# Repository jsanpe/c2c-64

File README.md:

# C2C-64
A Composite & S-Video to Component Video transcoder to feed older analog signals into your OSSC.

Designed with the C-64 in mind, it also supports composite and s-video signals from other systems, including the N64. A compatibility chart will soon be available in the wiki section of this project.

## Description

This is an open hardware implementation of a board to convert Composite and S-Video signals into Component video. The component output from C2C-64 can be directly connected to an OSSC, effectively adding compatibility with Composite and S-Video input to this great scaler.

C2C-64 was primarily design as a simple way to connect a C64 to and OSSC. Most of the testing has been done in this platform, and presets have been chosen with it in mind. I have conducted some tests with other machines (N64, SNES, Dreamcast), although not as extensive.

C2C-64 uses a simple pipeline of video decoder and encoder to transform the input composite or S-video signals into component video. What this means in practice is that the analog input is converted to digital format and fed to the encoder to transform it into a different analog signal. This conversion is NOT lossless. However, it enables anyone to conveniently hook such signals directly into the OSSC without tinkering with the internals of their devices. 

## Getting your C2C-64

This is an open project, in this repository you will find everything you need in order to build your own C2C-64.

It is important to note that building this requires ninja-grade soldering skills, especially to get those QFN ICs properly connected to the board. Also, sourcing some of the components may be a bit trickier than usual. In particular, the ADV7180 IC is unsupported by Analog anymore and probably AliExpress is the only place where it can be found at this point. There is an ADV7280(A) based version of the C2C (2R) that will be soon released, but the price of this IC is way more expensive.

I am in the process of building a first batch of 35 boards (version 1R3) that I will be selling to anyone interested in supporting the project. Reach me directly if you are interested (DM me directly through [twitter](https://twitter.com/jsanpe))

You can also support the project by donating through my KoFi page 

## Comparison to Koryuu

In terms of functionality, C2C-64 provides a similar experience to the commercial product [Koryuu](https://videogameperfection.com/products/koryuu-transcoder/). However, there are notable differences between C2C-64 and Koryuu:
- C2C-64 is fully Open and Free, both Software and Hardware. Note, C2C-64 is still WiP so some parts are either missing or still in beta.
- C2C-64 has been designed to be as affordable as possible. The PCB is a 50x50mm 4 layer design, for which you can normally get special deals on PCB manufacturers. With the current shortage of electronic parts, it is difficult to estimate the total BOM cost given the huge price fluctuations. It should be possible to get the board built for well under $50 in small amounts even in these adverse conditions (half the price of Koryuu).
- The video decoding IC in the C2C-64 is the older Adv7180, compared to the more modern Adv7280 of the Koryuu. I made extensive tests, and for the intent and purposes of this board I don't think the extra cost of Adv7280 (5x the price of Adv7180) is justified. This assumption holds as long as you connect the output to an OSSC, which has de-interlacing and scaling options way beyond the possibilities of the Adv7280. An Adv7280-based version of C2C-64  already exists and will be released at some point in the future (it needs more testing and firmware changes)
- C2C-64 adds a big number of usability features to the mix (described below) making it way more flexible in terms of configuration options

## User interface

One important improvement of C2C-64 over Koryuu is the inclusion of powerful interfacing options. The board provides three main ways of allowing user interaction:
- Side switches: There are 3 switches that allow the user to perform the two most common actions: alternating the source video signal between composite and S-video; and selecting configuration profiles stored in the board EEPROM.
- UART connection: A computer can be hooked up to the board using the uart pin headers available for this purpose. Using a VT100 compatible terminal, users can configure tenths of parameters about how the video decoding/encoding is performed using menus. Such settings can then be stored as profiles in the EEPROM to be easily accessed using the side switches.
- OLED Screen: The board supports the connection of an OPTIONAL 0.96'' oled display. When the board detected that an OLED display has been connected, it will show a reduced version of the menu system offered through the UART connection, making the use of a computer to configure settings completely unnecessary.

There are also 4 leds that are used to show important signals about the operation of the board

## Important notice

This project is still WiP. The repository contains only a beta version of the firmware required to run the board. Keep checking this page for updates.

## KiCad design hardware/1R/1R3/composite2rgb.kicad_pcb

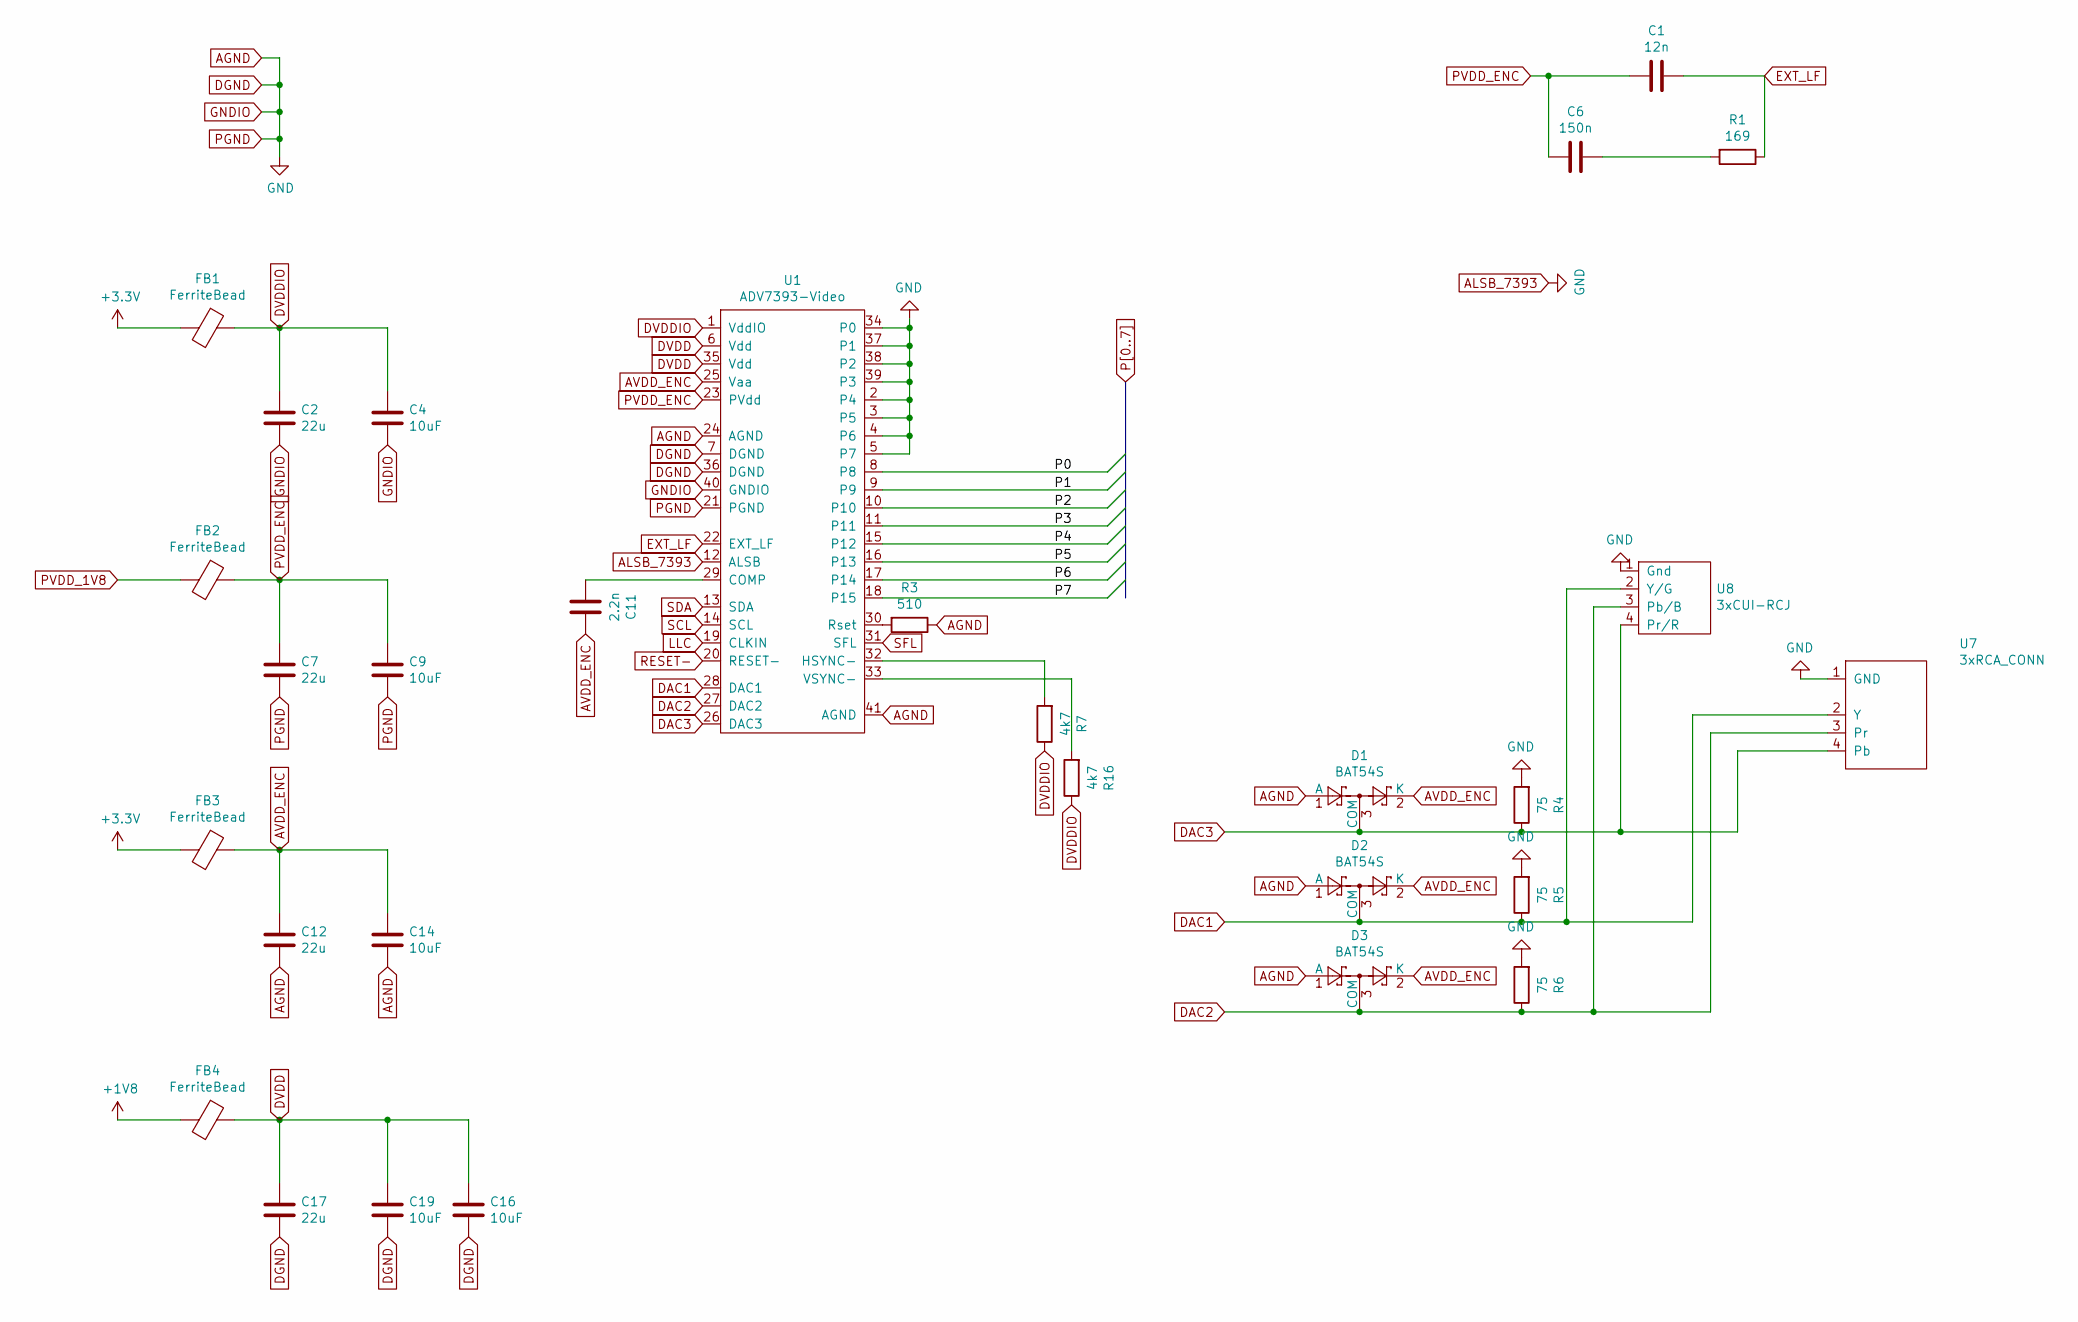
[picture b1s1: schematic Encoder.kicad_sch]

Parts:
C1: 12n; C_0603_1608Metric; LCSC_Part C1593
C2, C7, C12, C17: 22u; C_0805_2012Metric_Pad1.18x1.45mm_HandSolder; LCSC_Part C45783
C4, C9, C14, C16, C19: 10uF; C_0603_1608Metric; LCSC_Part C14663
C6: 150n; C_0603_1608Metric; LCSC_Part C21118
C11: 2.2n; C_0603_1608Metric; LCSC_Part C1604
D1, D2, D3: BAT54S; SOT-23
FB1, FB2, FB3, FB4: FerriteBead; L_0805_2012Metric; LCSC_Part C1015
R1: 169; R_0805_2012Metric; LCSC C22889
R3: 510; R_0805_2012Metric; LCSC C17734
R4, R5, R6: 75; R_0805_2012Metric; LCSC_Part C20638
R7, R16: 4k7; R_0603_1608Metric; LCSC_Part C23162
U1: ADV7393-Video; QFN-40-1EP_6x6mm_P0.5mm_EP4.6x4.6mm_ThermalVias; LCSC C662241
U7: 3xRCA_CONN; TRRS-PJ-320A
U8: 3xCUI-RCJ; 3xCUI_RCJ-041

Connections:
+1V8: FB4.2; also elsewhere on the board
+3.3V: FB1.2, FB3.2; also elsewhere on the board
AGND: C2.1, C4.1, C7.1, C9.1, C12.1, C14.1, C16.1, C17.1, C19.1, D1.1 (A), D2.1 (A), D3.1 (A), R3.1, R4.2, R5.2, R6.2, U1.2 (P4), U1.3 (P5), U1.4 (P6), U1.5 (P7), U1.7 (DGND), U1.12 (ALSB), U1.21 (PGND), U1.24 (AGND), U1.34 (P0), U1.36 (DGND), U1.37 (P1), U1.38 (P2), U1.39 (P3), U1.40 (GNDIO), U1.41 (AGND), U7.1 (GND), U8.1 (Gnd); also elsewhere on the board
AVDD_ENC: C11.2, C12.2, C14.2, D1.2 (K), D2.2 (K), D3.2 (K), FB3.1, U1.25 (Vaa)
DAC1: D2.3 (COM), R5.1, U1.28 (DAC1), U7.2 (Y), U8.2 (Y/G)
DAC2: D3.3 (COM), R6.1, U1.27 (DAC2), U7.3 (Pr), U8.3 (Pb/B)
DAC3: D1.3 (COM), R4.1, U1.26 (DAC3), U7.4 (Pb), U8.4 (Pr/R)
DVDD: C16.2, C17.2, C19.2, FB4.1, U1.6 (Vdd), U1.35 (Vdd); also elsewhere on the board
DVDDIO: C2.2, C4.2, FB1.1, R7.1, R16.1, U1.1 (VddIO); also elsewhere on the board
EXT_LF: C1.1, R1.1, U1.22 (EXT_LF)
LLC: U1.19 (CLKIN); also elsewhere on the board
unnamed: C6.1, R1.2
unnamed: C11.1, U1.29 (COMP)
unnamed: R7.2, U1.32 (HSYNC-)
unnamed: R3.2, U1.30 (Rset)
unnamed: R16.2, U1.33 (VSYNC-)
P0: U1.8; also elsewhere on the board
P1: U1.9; also elsewhere on the board
P2: U1.10; also elsewhere on the board
P3: U1.11; also elsewhere on the board
P4: U1.15 (P12); also elsewhere on the board
P5: U1.16 (P13); also elsewhere on the board
P6: U1.17 (P14); also elsewhere on the board
P7: U1.18 (P15); also elsewhere on the board
PVDD_1V8: FB2.2; also elsewhere on the board
PVDD_ENC: C1.2, C6.2, C7.2, C9.2, FB2.1, U1.23 (PVdd)
RESET-: U1.20 (RESET-); also elsewhere on the board
SCL: U1.14 (SCL); also elsewhere on the board
SDA: U1.13 (SDA); also elsewhere on the board
SFL: U1.31 (SFL); also elsewhere on the board

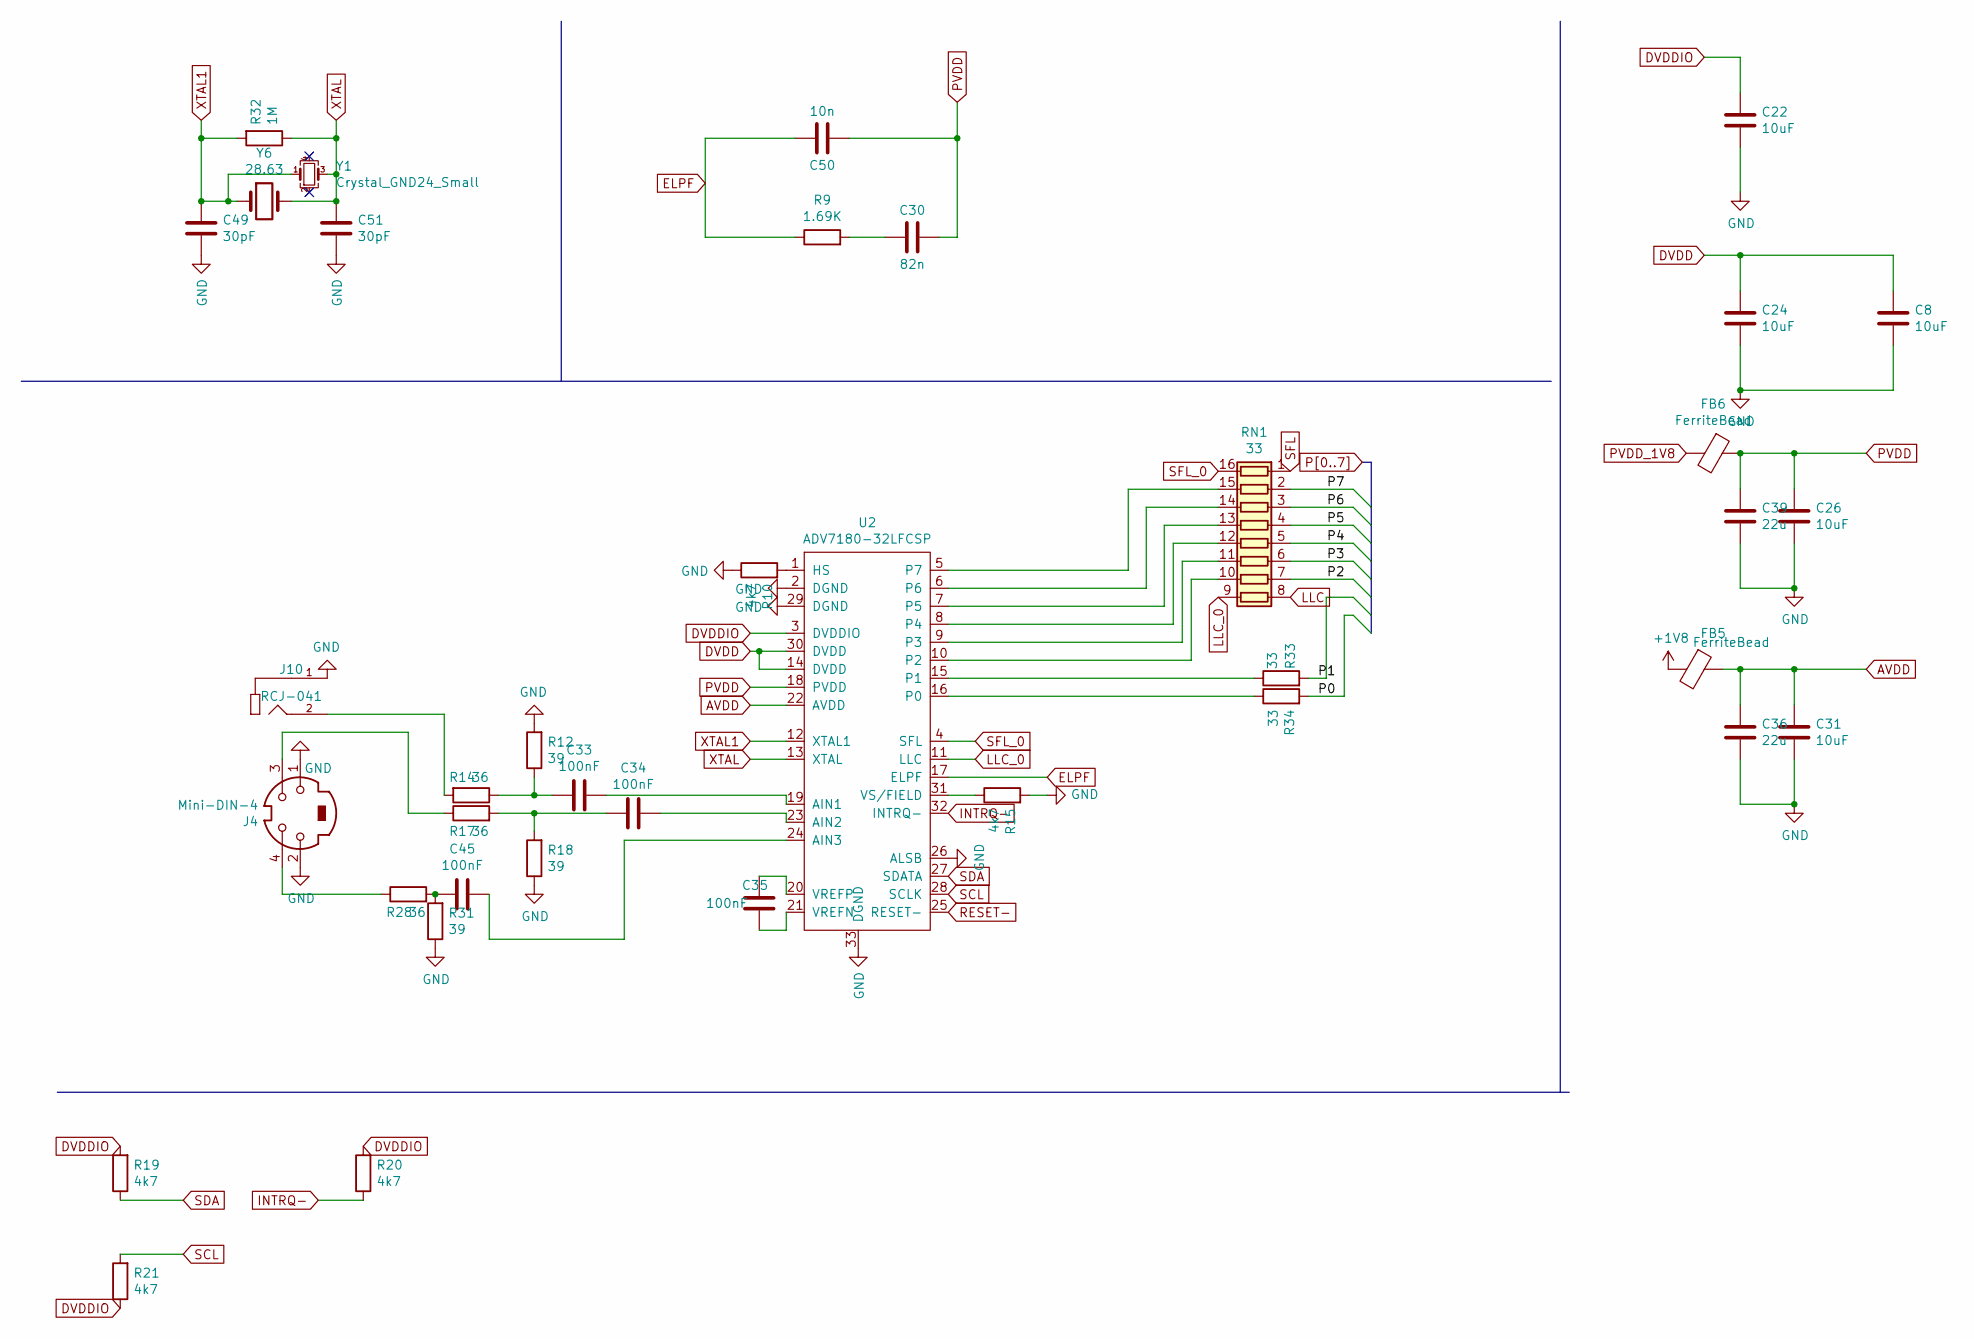
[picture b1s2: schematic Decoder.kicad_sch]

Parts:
C8, C22, C24, C26, C31: 10uF; C_0603_1608Metric; LCSC C19702
C30: 82n; C_0603_1608Metric; LCSC C107100
C33, C34, C35, C45: 100nF; C_0603_1608Metric; LCSC C14663
C36, C39: 22u; C_0805_2012Metric; LCSC C45783
C49, C51: 30pF; C_0603_1608Metric; LCSC_Part C57112
C50: 10n; C_0603_1608Metric; LCSC C57112
FB5, FB6: FerriteBead; L_0805_2012Metric; LCSC C1017
J4: Mini-DIN-4; CUI_MD-50S
J10: RCJ-041; CUI_RCJ-041
R9: 1.69K; R_0603_1608Metric; LCSC C22846
R10, R15, R19, R20, R21: 4k7; R_0603_1608Metric; LCSC C23162
R12, R18, R31: 39; R_0805_2012Metric; LCSC C186443
R14, R17, R28: 36; R_0805_2012Metric; LCSC C186442
R32: 1M; R_0603_1608Metric; LCSC C22935
R33, R34: 33; R_0805_2012Metric; LCSC C17634
RN1: 33; RESCAXE50P380X160X55-16N; LCSC C78520
U2: ADV7180-32LFCSP; LFCSP-32-1EP_5x5mm_P0.5mm_EP3.1x3.1mm_ThermalVias; LCSC C459884
Y1: Crystal_GND24_Small; Crystal_SMD_3225-4Pin_3.2x2.5mm; LCSC C136080
Y6: 28.63; Crystal_C38-LF_D3.0mm_L8.0mm_Vertical

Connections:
+1V8: FB5.2; also elsewhere on the board
AGND: C8.1, C22.1, C24.1, C26.1, C31.1, C36.1, C39.1, C49.1, C51.1, J4.1, J4.2, J10.1, R10.1, R12.2, R15.2, R18.1, R31.1, U2.2 (DGND), U2.26 (ALSB), U2.29 (DGND), U2.33 (DGND); also elsewhere on the board
AVDD: C31.2, C36.2, FB5.1, U2.22 (AVDD)
DVDD: C8.2, C24.2, U2.14 (DVDD), U2.30 (DVDD); also elsewhere on the board
DVDDIO: C22.2, R19.2, R20.2, R21.1, U2.3 (DVDDIO); also elsewhere on the board
ELPF: C50.2, R9.1, U2.17 (ELPF)
INTRQ-: R20.1, U2.32 (INTRQ-)
LLC: RN1.8 (R8.1); also elsewhere on the board
LLC_0: RN1.9 (R8.2), U2.11 (LLC)
unnamed: C30.1, R9.2
unnamed: C33.2, R12.1, R14.1
unnamed: C34.2, R17.2, R18.2
unnamed: C45.2, R28.2, R31.2
unnamed: J4.3, R17.1
unnamed: J4.4, R28.1
unnamed: J10.2, R14.2
unnamed: RN1.15 (R2.2), U2.5 (P7)
unnamed: RN1.14 (R3.2), U2.6
unnamed: RN1.13 (R4.2), U2.7 (P5)
unnamed: RN1.12 (R5.2), U2.8 (P4)
unnamed: RN1.11 (R6.2), U2.9 (P3)
unnamed: RN1.10 (R7.2), U2.10 (P2)
unnamed: C33.1, U2.19 (AIN1)
unnamed: C34.1, U2.23 (AIN2)
unnamed: C45.1, U2.24 (AIN3)
unnamed: R10.2, U2.1 (HS)
unnamed: R34.1, U2.16 (P0)
unnamed: R33.1, U2.15 (P1)
unnamed: C35.2, U2.21 (VREFN)
unnamed: C35.1, U2.20 (VREFP)
unnamed: R15.1, U2.31 (VS/FIELD)
P0: R34.2; also elsewhere on the board
P1: R33.2; also elsewhere on the board
P2: RN1.7 (R7.1); also elsewhere on the board
P3: RN1.6 (R6.1); also elsewhere on the board
P4: RN1.5 (R5.1); also elsewhere on the board
P5: RN1.4 (R4.1); also elsewhere on the board
P6: RN1.3 (R3.1); also elsewhere on the board
P7: RN1.2 (R2.1); also elsewhere on the board
PVDD: C26.2, C30.2, C39.2, C50.1, FB6.1, U2.18 (PVDD)
PVDD_1V8: FB6.2; also elsewhere on the board
RESET-: U2.25 (RESET-); also elsewhere on the board
SCL: R21.2, U2.28 (SCLK); also elsewhere on the board
SDA: R19.1, U2.27 (SDATA); also elsewhere on the board
SFL: RN1.1 (R1.1); also elsewhere on the board
SFL_0: RN1.16 (R1.2), U2.4 (SFL)
XTAL: C51.2, R32.1, U2.13 (XTAL), Y1.3, Y6.2
XTAL1: C49.2, R32.2, U2.12 (XTAL1), Y1.1, Y6.1

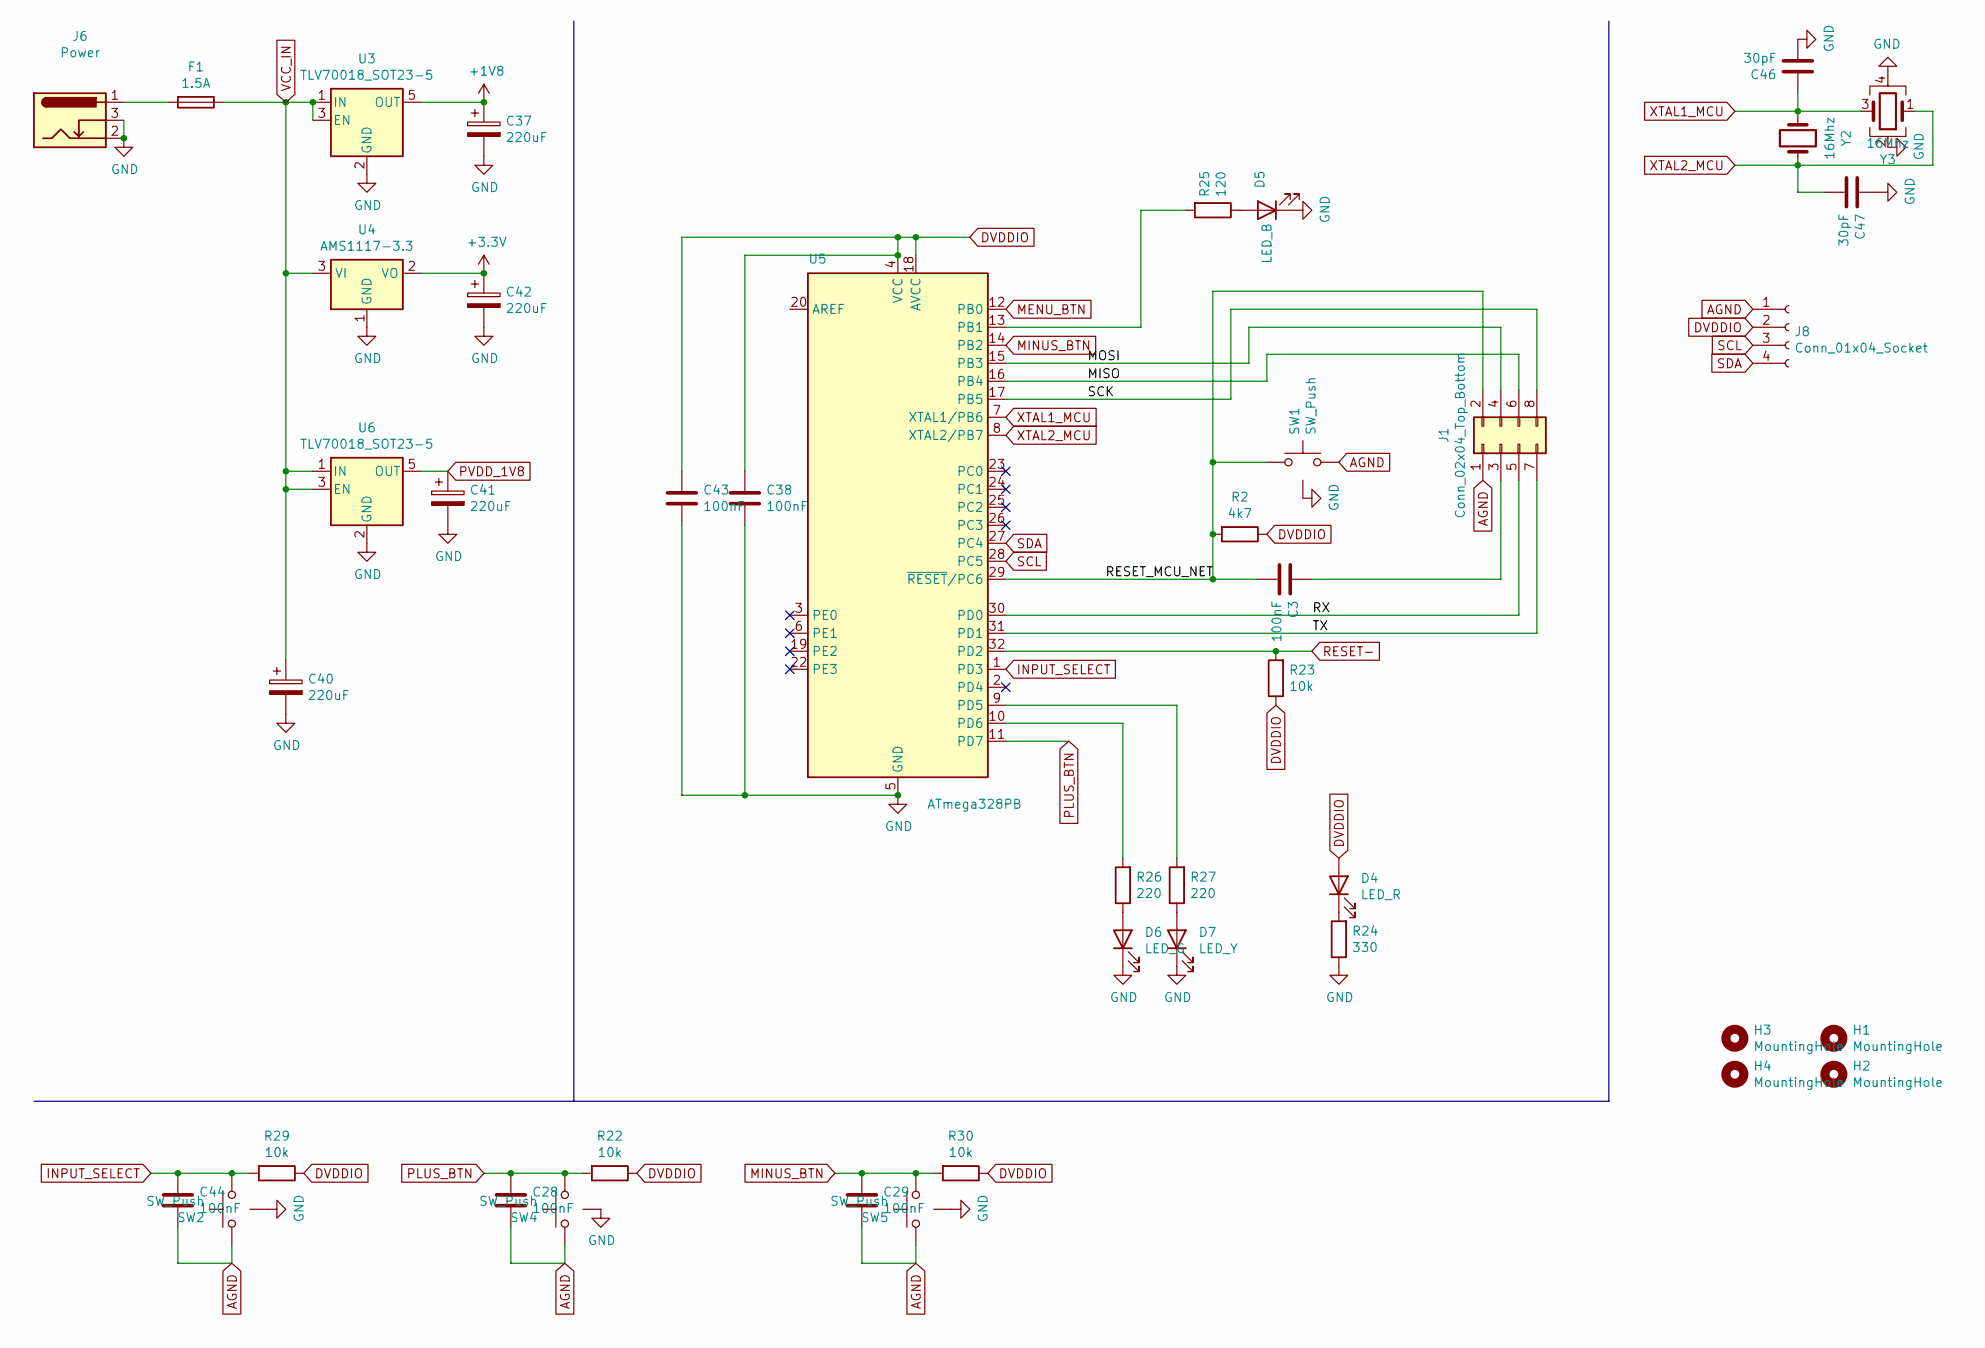
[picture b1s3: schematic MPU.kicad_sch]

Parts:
C3, C38, C43: 100nF; C_0603_1608Metric; LCSC_Part C14663
C28, C29, C44: 100nF; C_0402_1005Metric; LCSC_Part C19666
C37, C40, C41, C42: 220uF; C_Radial_D6.3mm_H5.0mm_P2.50mm
C46, C47: 30pF; C_0603_1608Metric; LCSC_Part C57112
D4: LED_R; LED_0805_2012Metric; LCSC_Part C72038
D5: LED_B; LED_0805_2012Metric; LCSC_Part C72041
D6: LED_G; LED_0805_2012Metric; LCSC_Part C72043
D7: LED_Y; LED_0805_2012Metric; LCSC_Part C2286
F1: 1.5A; Fuse_0402_1005Metric; LCSC C311043
H1, H2, H3, H4: MountingHole; MountingHole_2.5mm
J1: Conn_02x04_Top_Bottom; PinHeader_2x04_P2.54mm_Vertical
J6: Power; BarrelJack_Horizontal
J8: Conn_01x04_Socket; PinSocket_1x04_P2.54mm_Vertical
R2: 4k7; R_0603_1608Metric; LCSC_Part C23162
R22, R29, R30: 10k; R_0402_1005Metric; LCSC_Part C23162
R23: 10k; R_0603_1608Metric; LCSC_Part C25804
R24: 330; R_0603_1608Metric; LCSC_Part C22962
R25: 120; R_0603_1608Metric; LCSC_Part C22787
R26, R27: 220; R_0603_1608Metric; LCSC_Part C22962
SW1, SW2, SW4, SW5: SW_Push; mini-btn; LCSC C455261
U3, U6: TLV70018_SOT23-5; SOT-23-5
U4: AMS1117-3.3; SOT-223-3_TabPin2; LCSC_Part C6186 (basic stockout)
U5: ATmega328PB; QFN-32-1EP_5x5mm_P0.5mm_EP3.1x3.1mm; LCSC C967933
Y2: 16Mhz; Crystal_C38-LF_D3.0mm_L8.0mm_Vertical
Y3: 16Mhz; Crystal_SMD_3225-4Pin_3.2x2.5mm; LCSC_Part C13738

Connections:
+1V8: C37.1, U3.5 (OUT); also elsewhere on the board
+3.3V: C42.1, U4.2 (VO); also elsewhere on the board
/Control/MISO: J1.6, U5.16 (PB4)
/Control/MOSI: J1.4, U5.15 (PB3)
/Control/RESET_MCU_NET: C3.1, J1.2, R2.2, SW1.1, U5.29 (~RESET/PC6)
/Control/RX: J1.5, U5.30 (PD0)
/Control/SCK: J1.8, U5.17 (PB5)
/Control/TX: J1.7, U5.31 (PD1)
AGND: C28.1, C29.1, C37.2, C38.2, C40.2, C41.2, C42.2, C43.2, C44.1, C46.1, C47.2, D5.1 (K), D6.1 (K), D7.1 (K), J1.1, J6.2, J6.3, J8.1, R24.1, SW1.2, SW1.3 (Gnd), SW2.1, SW2.3 (Gnd), SW4.1, SW4.3 (Gnd), SW5.1, SW5.3 (Gnd), U3.2 (GND), U4.1 (GND), U5.5 (GND), U5.21 (GND), U5.33 (GND), U6.2 (GND), Y3.2, Y3.4; also elsewhere on the board
DVDDIO: C38.1, C43.1, D4.2 (A), J8.2, R2.1, R22.1, R23.1, R29.1, R30.1, U5.4 (VCC), U5.18 (AVCC); also elsewhere on the board
INPUT_SELECT: C44.2, R29.2, SW2.2, U5.1 (PD3)
MENU_BTN: U5.12 (PB0)
MINUS_BTN: C29.2, R30.2, SW5.2, U5.14 (PB2)
unnamed: D4.1 (K), R24.2
unnamed: D5.2 (A), R25.1
unnamed: D6.2 (A), R26.1
unnamed: D7.2 (A), R27.1
unnamed: F1.2, J6.1
unnamed: C3.2, J1.3
unnamed: R25.2, U5.13 (PB1)
unnamed: R27.2, U5.9 (PD5)
unnamed: R26.2, U5.10 (PD6)
PLUS_BTN: C28.2, R22.2, SW4.2, U5.11 (PD7)
PVDD_1V8: C41.1, U6.5 (OUT); also elsewhere on the board
RESET-: R23.2, U5.32 (PD2); also elsewhere on the board
SCL: J8.3, U5.28 (PC5); also elsewhere on the board
SDA: J8.4, U5.27 (PC4); also elsewhere on the board
VCC_IN: C40.1, F1.1, U3.1 (IN), U3.3 (EN), U4.3 (VI), U6.1 (IN), U6.3 (EN)
XTAL1_MCU: C46.2, U5.7 (XTAL1/PB6), Y2.1, Y3.3
XTAL2_MCU: C47.1, U5.8 (XTAL2/PB7), Y2.2, Y3.1

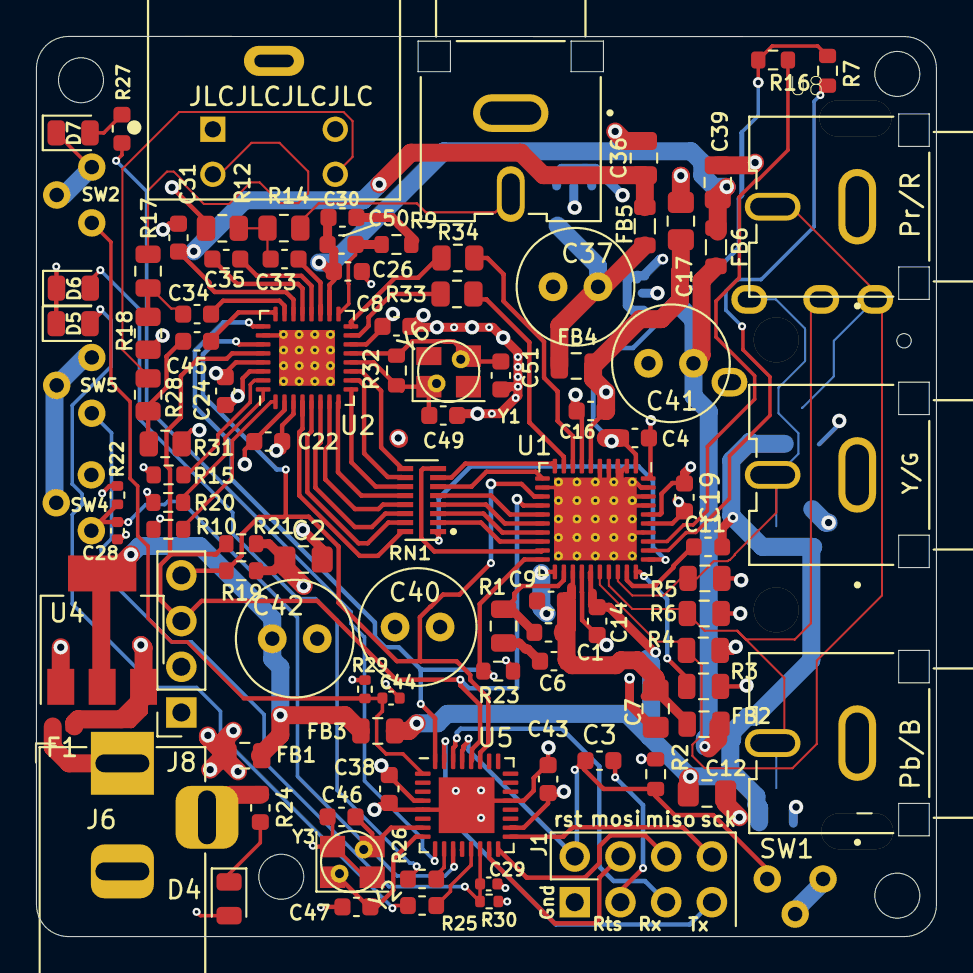
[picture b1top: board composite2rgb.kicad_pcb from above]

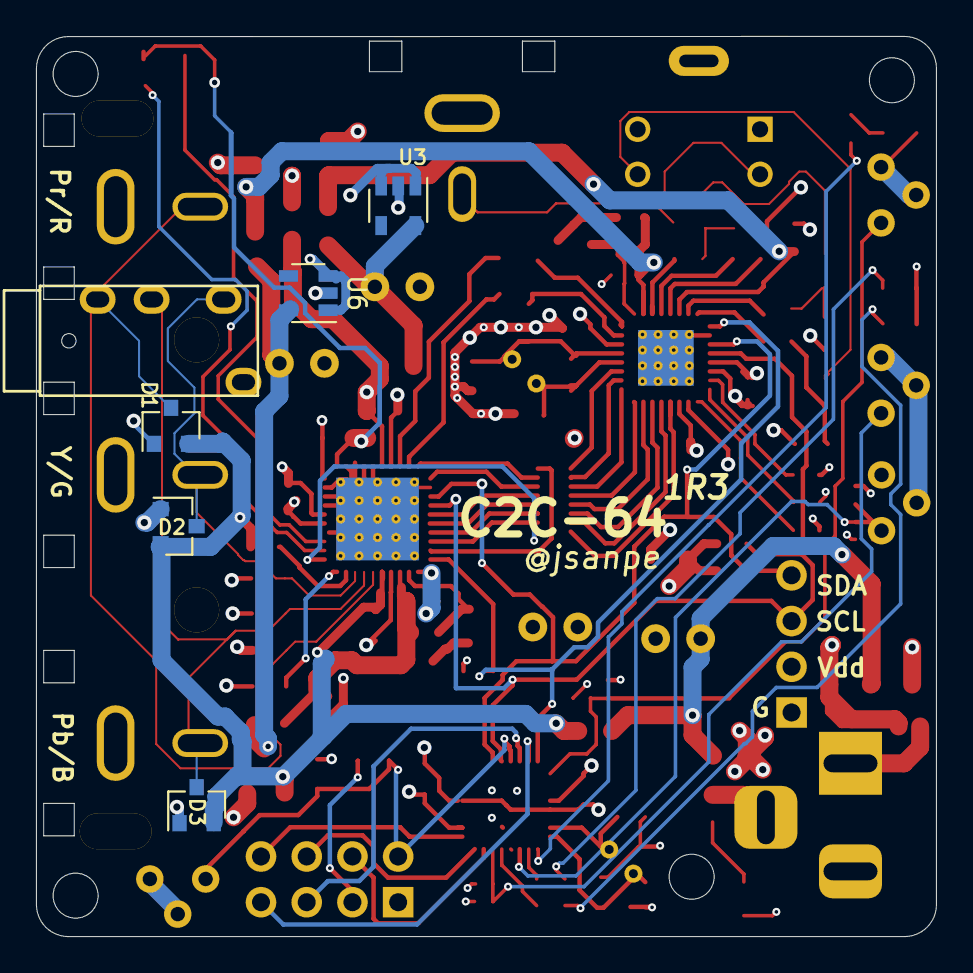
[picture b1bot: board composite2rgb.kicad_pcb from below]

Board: 4 copper layers, 50.0 x 50.0 mm, 110 parts (6 on the bottom side), 81 nets.

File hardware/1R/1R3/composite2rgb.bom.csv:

"Value","Designator","Footprint","Comments"
"12n","C1","Capacitor_SMD:C_0603_1608Metric","<=5% tolerance, >=X7R"
"2.2n","C11","Capacitor_SMD:C_0603_1608Metric",
"22u","C2,C7,C12,C17","Capacitor_SMD:C_0805_2012Metric",
"82n","C30","Capacitor_SMD:C_0603_1608Metric","<=5% tolerance, >=X7R"
"100nF","C3,C33,C34,C35,C38,C43,C45","Capacitor_SMD:C_0603_1608Metric",
"22u","C36,C39","Capacitor_SMD:C_0805_2012Metric",
"10uF","C4,C8,C9,C14,C16,C19,C22,C24,C26,C31","Capacitor_SMD:C_0603_1608Metric",
"220uF","C37,C40,C41,C42","Capacitor_THT:C_Radial_D6.3mm_H5.0mm_P2.50mm",
"100nF","C28,C29,C44","Capacitor_SMD:C_0402_1005Metric",
"30pF","C46,C47,C49,C51","Capacitor_SMD:C_0603_1608Metric",
"10n","C50","Capacitor_SMD:C_0603_1608Metric","<=5% tolerance, >=X7R"
"150n","C6","Capacitor_SMD:C_0603_1608Metric","<=5% tolerance, >=X7R"
"BAT54S","D1,D2,D3","Package_TO_SOT_SMD:SOT-23",
"LED_R","D4","LED_SMD:LED_0805_2012Metric",
"LED_B","D5","LED_SMD:LED_0805_2012Metric",
"LED_G","D6","LED_SMD:LED_0805_2012Metric",
"LED_Y","D7","LED_SMD:LED_0805_2012Metric",
"1.5A","F1","Fuse:Fuse_0402_1005Metric",
"Ferrite_Bead","FB1,FB2,FB3,FB4,FB5,FB6","Inductor_SMD:L_0805_2012Metric",
"MountingHole","H1,H2,H3,H4","MountingHole:MountingHole_2.5mm",
"Conn_02x04_Top_Bottom","J1","Connector_PinHeader_2.54mm:PinHeader_2x04_P2.54mm_Vertical",
"RCJ-041","J10","RCJ-041:CUI_RCJ-041",
"Mini-DIN-4","J4","RCJ-041:CUI_MD-50S",
"Power","J6","Connector_BarrelJack:BarrelJack_Horizontal",
"Conn_01x04_Female","J8","Connector_PinSocket_2.54mm:PinSocket_1x04_P2.54mm_Vertical",
"169","R1","Resistor_SMD:R_0805_2012Metric",
"39","R12,R18,R31","Resistor_SMD:R_0805_2012Metric",
"36","R14,R17,R28","Resistor_SMD:R_0805_2012Metric",
"10k","R23","Resistor_SMD:R_0603_1608Metric",
"330","R24","Resistor_SMD:R_0603_1608Metric",
"120","R25","Resistor_SMD:R_0603_1608Metric",
"220","R26,R27","Resistor_SMD:R_0603_1608Metric",
"10k","R22,R29,R30","Resistor_SMD:R_0402_1005Metric",
"510","R3","Resistor_SMD:R_0805_2012Metric",
"1M","R32","Resistor_SMD:R_0603_1608Metric",
"33","R33,R34","Resistor_SMD:R_0805_2012Metric",
"75","R4,R5,R6","Resistor_SMD:R_0805_2012Metric",
"4k7","R2,R7,R10,R15,R16,R19,R20,R21","Resistor_SMD:R_0603_1608Metric",
"1.69K","R9","Resistor_SMD:R_0603_1608Metric",
"33","RN1","RCJ-041:RESCAXE50P380X160X55-16N",
"SW_Push","SW1,SW2,SW4,SW5","Button_Switch_THT:mini-btn",
"ADV7393-Video","U1","Package_DFN_QFN:QFN-40-1EP_6x6mm_P0.5mm_EP4.6x4.6mm_ThermalVias",
"ADV7180-32LFCSP","U2","Package_CSP:LFCSP-32-1EP_5x5mm_P0.5mm_EP3.1x3.1mm_ThermalVias",
"TLV70018_SOT23-5","U3,U6","Package_TO_SOT_SMD:SOT-23-5",
"AMS1117-3.3","U4","Package_TO_SOT_SMD:SOT-223-3_TabPin2",
"ATmega328PB-MU","U5","Package_DFN_QFN:QFN-32-1EP_5x5mm_P0.5mm_EP3.1x3.1mm",
"3xRCA_CONN","U7","RCJ-041:TRRS-PJ-320A",
"3xCUI-RCJ","U8","RCJ-041:3xCUI_RCJ-041",
"Crystal_GND24_Small","Y1","Crystal:Crystal_SMD_3225-4Pin_3.2x2.5mm",
"16Mhz","Y2","Crystal:Crystal_C38-LF_D3.0mm_L8.0mm_Vertical",
"16Mhz","Y3","Crystal:Crystal_SMD_3225-4Pin_3.2x2.5mm",
"28.63","Y6","Crystal:Crystal_C38-LF_D3.0mm_L8.0mm_Vertical",

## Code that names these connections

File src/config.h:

#pragma once

//CONSTANTS
#define ADV7280 0
#define ADV7180Q32 1

//CONFIG
#define DECODER ADV7180Q32
#define DEFAULT_SOURCE CVBS
#define DEFAULT_FREERUN false

//BOARD VERSION
#define BOARD_VERSION_MAJOR 3
#define BOARD_VERSION_MINOR 0

//UART
#define SERIAL_PORT_SPEED 38400

//OLED SUPPORT
#define OLED_ENABLED

#if (BOARD_VERSION_MAJOR==2)
//TODO
#elif (BOARD_VERSION_MAJOR==3)
//PINS
#define LED_INPUT PIN_PD5
#define LED_LOCK PIN_PD6
#define LED_SIGNAL PIN_PB1

#define BTN_INPUT PIN_PD3
//#define BTN_MENU PB0
#define BTN_MINUS PIN_PB2 
#define BTN_PLUS PIN_PD7
#define RESET_ADV PIN_PD2
#endif

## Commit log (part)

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2021-09-17 Board image
2021-09-17 README fixed
2021-09-17 More images
2021-09-17 Create LICENSE
2021-10-15 1R3: gerbers and bom Images
2021-10-16 Better board images
2021-10-16 new image
2021-11-01 RGB Mode Oled Info screen changed to fit screen
2021-12-02 New images
2021-12-31 New menu system and button management code
2022-01-28 Case for 1R3
2022-01-28 Refactor menu system
2022-01-28 Simplified menu system
2022-01-30 Remove debug messages
2024-01-22 Interactive BOM added
2024-02-20 Update platformio.ini
    Support for new urboot bootloader of MiniCore
